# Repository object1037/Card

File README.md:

# Card

A PCB business card that functions as a Bluetooth trackpad.

* BLE module: [ISP1907-LL](https://www.insightsip.com/products/bluetooth-le-modules/isp1907) (SoC: nRF52811)
* Touch controller: [MTCH6102](https://www.microchip.com/en-us/product/mtch6102)
* Power: CR2032

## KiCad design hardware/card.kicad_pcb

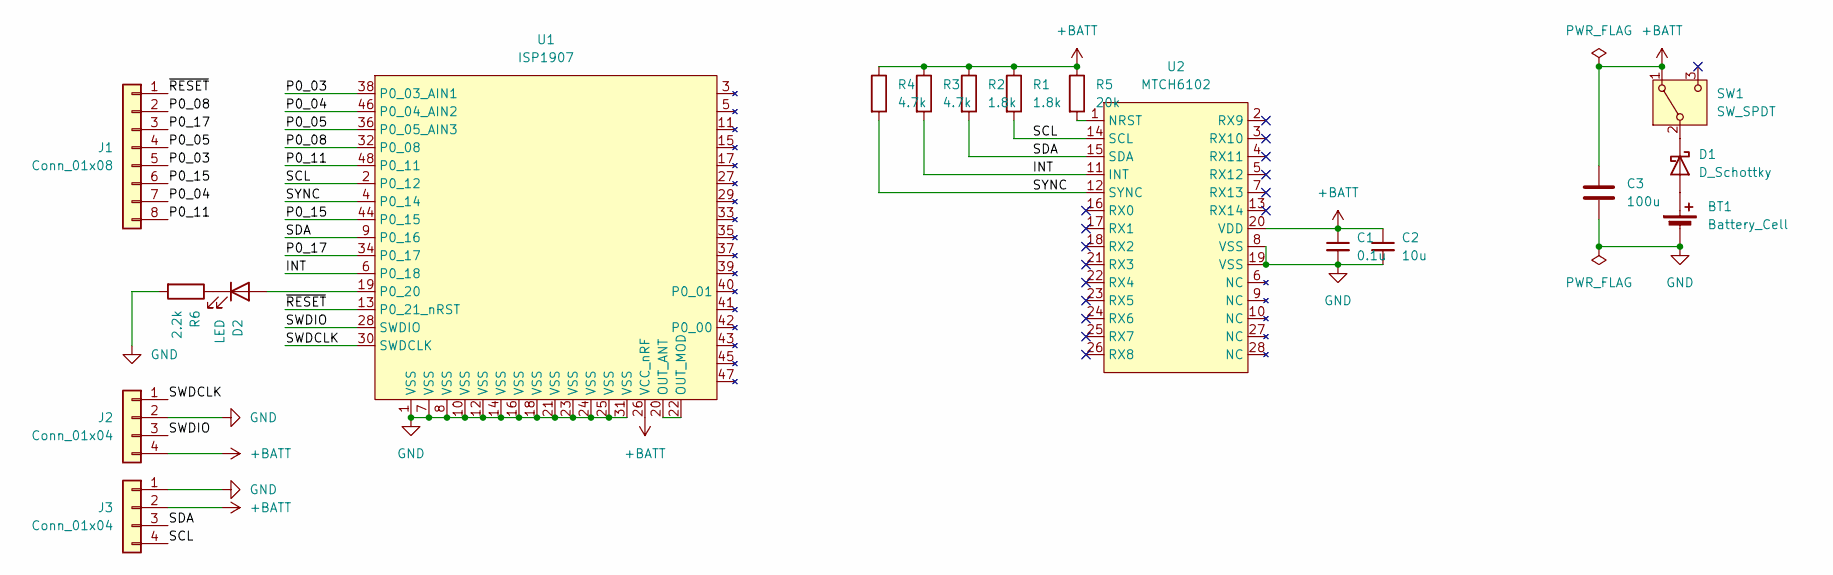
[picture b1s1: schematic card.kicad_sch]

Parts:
BT1: Battery_Cell; BatteryHolder_Multicomp_BC-2001_1x2032
C1: 0.1u; C_0402_1005Metric
C2: 10u; C_0402_1005Metric
C3: 100u; C_1206_3216Metric
D1: D_Schottky; D_SOD-123
D2: LED; LED_0603_1608Metric
J1: Conn_01x08; PinHeader_1x08_P2.54mm_Vertical
J2: Conn_01x04; PinHeader_1x04_P2.54mm_Vertical
J3: Conn_01x04; JST_SH_SM04B-SRSS-TB_1x04-1MP_P1.00mm_Horizontal
R1, R2: 1.8k; R_0603_1608Metric
R3, R4: 4.7k; R_0603_1608Metric
R5: 20k; R_0603_1608Metric
R6: 2.2k; R_0603_1608Metric
SW1: SW_SPDT; SW_SPDT_PCM12
U1: ISP1907
U2: MTCH6102; SSOP-28_5.3x10.2mm_P0.65mm

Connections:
+BATT: C1.1, C2.1, C3.1, J2.4, J3.2, R1.1, R2.1, R3.1, R4.1, R5.1, SW1.1 (A), U1.26 (VCC_nRF), U2.20 (VDD)
/INT: R3.2, U1.6 (P0_18), U2.11 (INT)
/P0_03: J1.5, U1.38 (P0_03_AIN1)
/P0_04: J1.7, U1.46 (P0_04_AIN2)
/P0_05: J1.4, U1.36 (P0_05_AIN3)
/P0_08: J1.2, U1.32 (P0_08)
/P0_11: J1.8, U1.48 (P0_11)
/P0_15: J1.6, U1.44 (P0_15)
/P0_17: J1.3, U1.34 (P0_17)
/SCL: J3.4, R1.2, U1.2 (P0_12), U2.14 (SCL)
/SDA: J3.3, R2.2, U1.9 (P0_16), U2.15 (SDA)
/SWDCLK: J2.1, U1.30 (SWDCLK)
/SWDIO: J2.3, U1.28 (SWDIO)
/SYNC: R4.2, U1.4 (P0_14), U2.12 (SYNC)
/~RESET: J1.1, U1.13 (P0_21_nRST)
GND: BT1.2 (-), C1.2, C2.2, C3.2, J2.2, J3.1, R6.2, U1.1 (VSS), U1.7 (VSS), U1.8 (VSS), U1.10 (VSS), U1.12 (VSS), U1.14 (VSS), U1.16 (VSS), U1.18 (VSS), U1.21 (VSS), U1.23 (VSS), U1.24 (VSS), U1.25 (VSS), U1.31 (VSS), U2.8 (VSS), U2.19 (VSS)
unnamed: BT1.1 (+), D1.2 (A)
unnamed: D1.1 (K), SW1.2 (B)
unnamed: D2.2 (A), U1.19 (P0_20)
unnamed: D2.1 (K), R6.1
unnamed: U1.20 (OUT_ANT), U1.22 (OUT_MOD)
unnamed: R5.2, U2.1 (NRST)

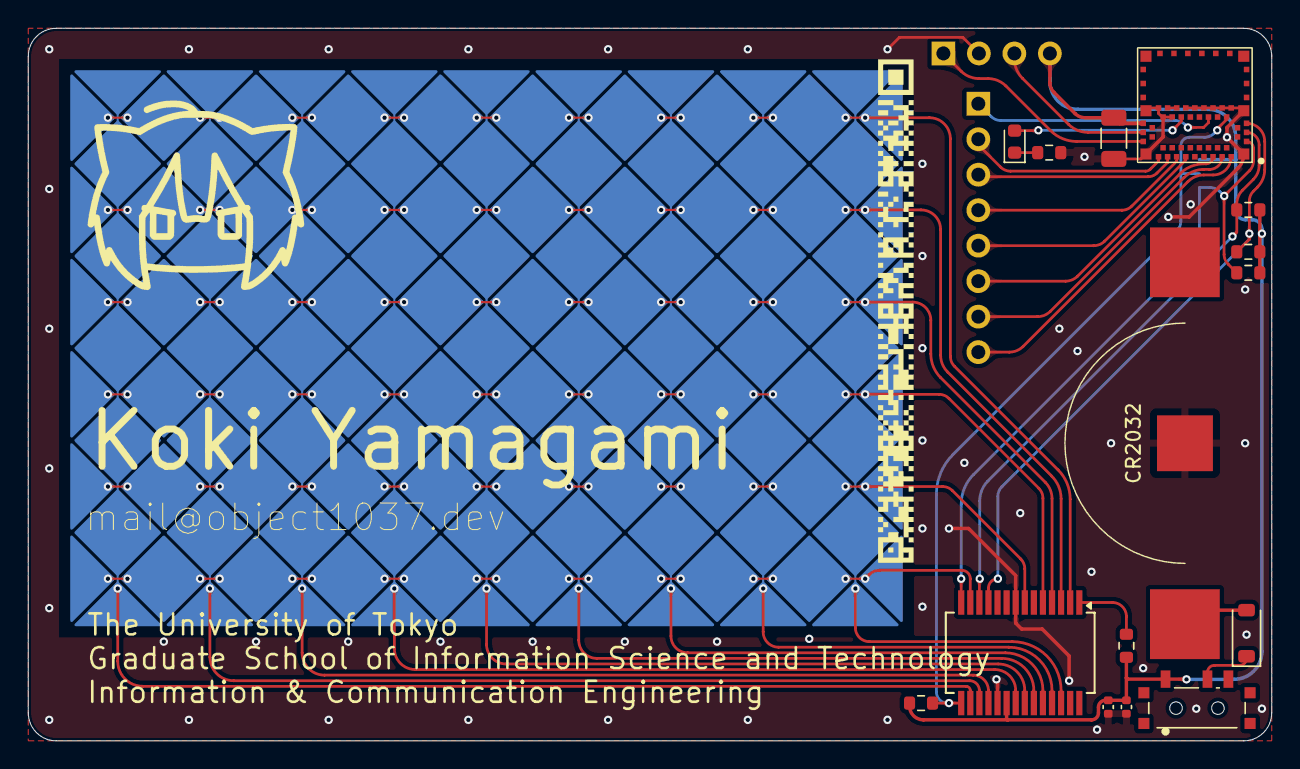
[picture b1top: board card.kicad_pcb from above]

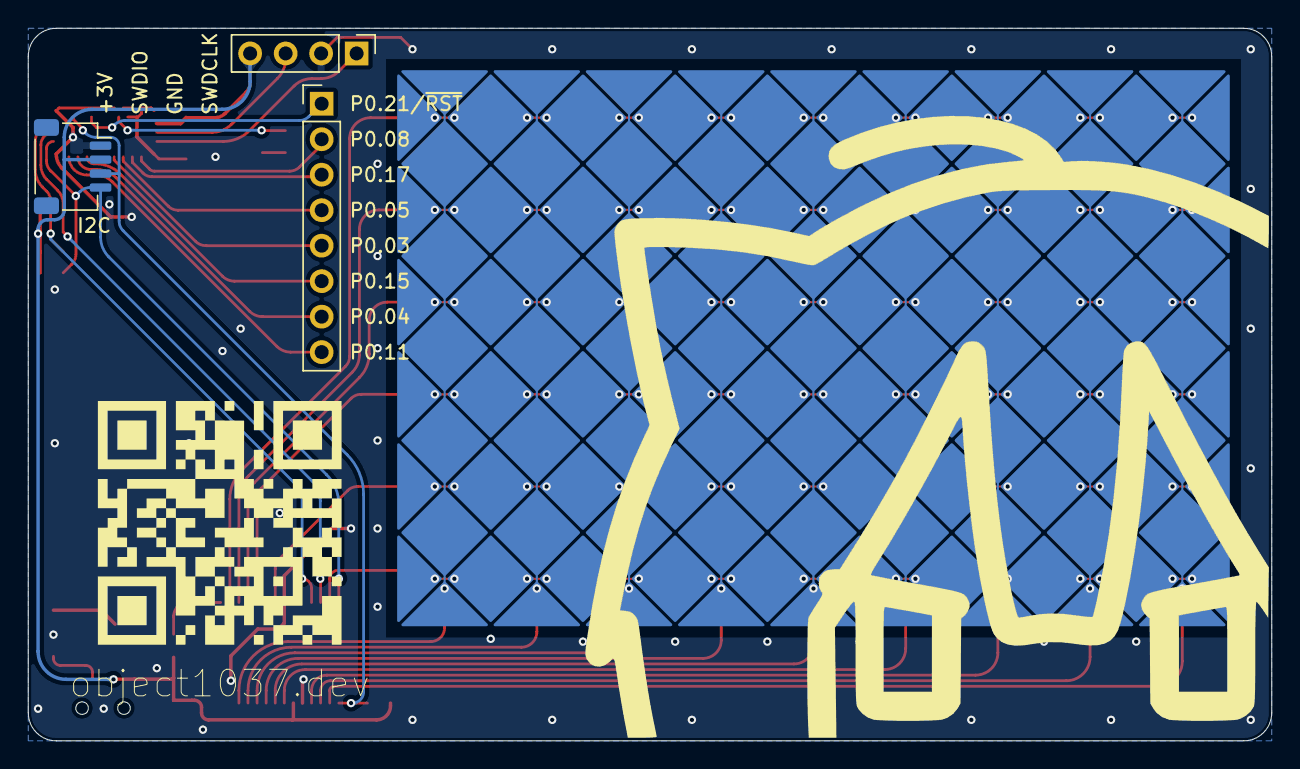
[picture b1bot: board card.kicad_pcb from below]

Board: 2 copper layers, 89.0 x 51.0 mm, 18 parts (3 on the bottom side), 22 nets.

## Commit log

2025-06-06 init
2025-06-06 update isp1907 symbol
2025-06-07 basic schematic
2025-06-07 basic pcb layout
2025-06-10 add qwiic conn and fillet traces
2025-06-10 update zone setting
2025-06-13 update silk
2025-06-13 add esd guard
2025-06-15 plot gerber
2025-06-16 add README
2025-06-19 add switch
2025-06-19 update production files
2025-06-19 add teardrops
2025-06-26 organize folder
2025-06-30 init with ncs
2025-06-30 LED blink
2025-06-30 enable rtt logging
2025-06-30 read touch data
2025-06-30 fix bug
2025-06-30 use bulk read
2025-06-30 interrupt test
2025-06-30 use polling for now
2025-06-30 ble advertising
2025-06-30 connect via ble
2025-06-30 minor fix
2025-07-02 add basic hid codes
2025-07-04 it works
2025-07-04 use just works security
2025-07-04 simplify
2025-07-04 separate files
2025-07-04 calculate pointer movement when touch is continuous
2025-07-04 update descriptor to use 10-bit resolution
2025-07-04 add click
2025-07-05 reduce image size
2025-07-05 update schematic pdf
2025-08-07 update kicad version
2025-08-08 save bond info in nvm
2025-08-08 change idle period of mtch6102 on boot
2025-08-08 prepare for interrupt-base operation
2025-08-08 move board defconfig to Kconfig.defconfig
2025-08-08 use work to offload led toggle from isr
2025-08-08 handle i2c in work handler
2025-08-08 handle gestures
2025-09-13 support right click with hold
